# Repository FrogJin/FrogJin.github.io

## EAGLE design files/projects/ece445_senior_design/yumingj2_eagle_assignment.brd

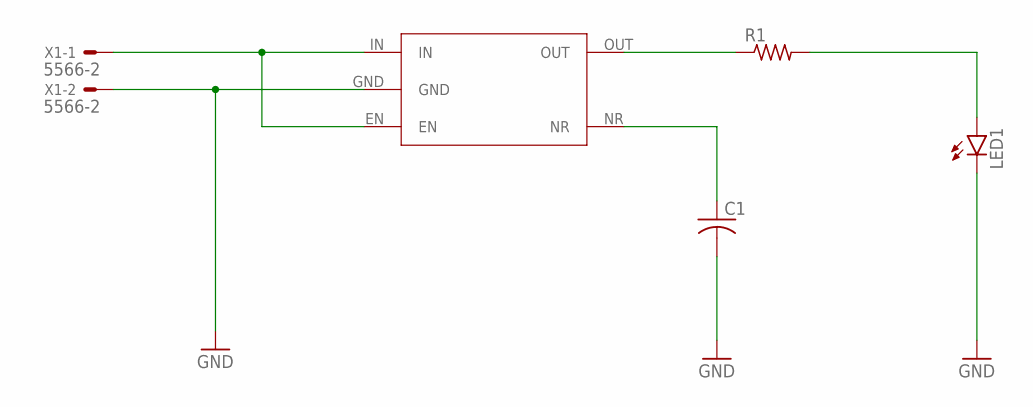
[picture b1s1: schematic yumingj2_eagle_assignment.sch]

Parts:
C1: C-US025-024X044; C025-024X044
LED1: LEDLSU260; LSU260
R1: R-US_0204/7; 0204/7
U$1: TPS799
X1: 5566-2

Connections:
GND: C1.2, LED1.K (C), U$1.GND, X1.2
unnamed: U$1.EN, U$1.IN, X1.1
unnamed: R1.1, U$1.OUT
unnamed: LED1.A, R1.2
unnamed: C1.1, U$1.NR

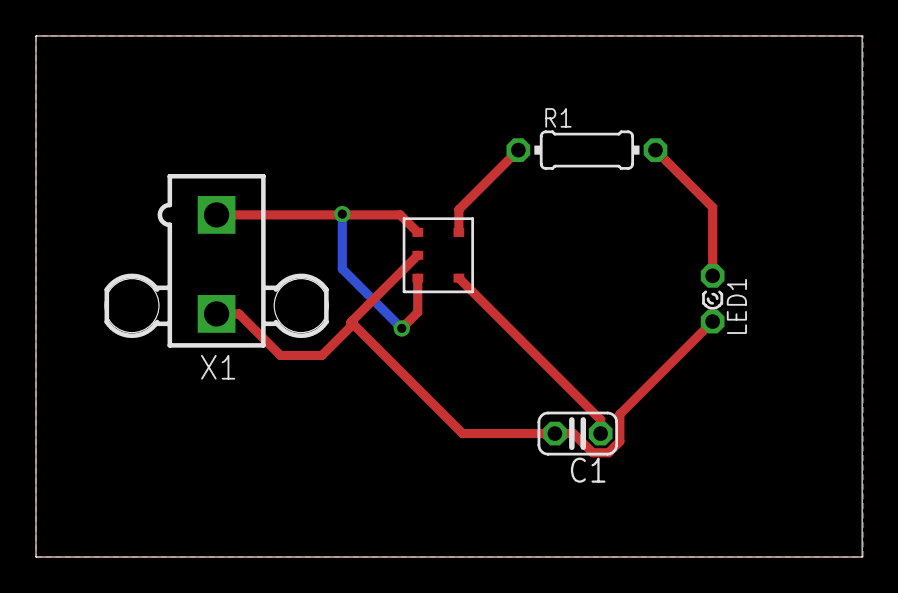
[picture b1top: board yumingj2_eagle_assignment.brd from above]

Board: 2 copper layers, 45.9 x 28.9 mm, 5 parts (0 on the bottom side), 5 nets.

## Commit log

2020-09-21 Create index.html
    Add dummy html file
2020-09-21 migrate portfolio page to github
2020-09-21 updating file links
2021-01-10 Winter updates. ME495 project added.
2021-01-12 New Chinese font added.
2021-01-12 me449 project added. Files clean up.
2021-01-13 me314 project added
2021-01-13 me315 project added
2021-03-15 unique urls for projects
2021-03-15 update homepage projects demo style
2021-03-15 fix homepage size compatibility
2021-03-16 me499 modal added
2021-03-16 me499 figures added
2021-03-16 me499 add demo 2
2021-03-16 future works added
2021-12-09 Master final project added
2021-12-10 swap mfp version 1 & 2
2021-12-11 revise mfp text
2022-01-16 update resume
